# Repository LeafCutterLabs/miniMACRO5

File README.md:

# miniMACRO5
QMK-powered macropad based on Arduino Pro Micro. Supports a mix of up to 5 rotary encoders or mechanical switches with optional RGB underglow.

<br>

## Bill of materials (BOM)
### Required components
1. Arduino Pro Micro with headers - available from SparkFun, eBay, Amazon, etc.
2. Rotary encoders - Bourns PEC12R and PEC11R, Alps, and the cheap Chinese versions have been tested. Any quadrature encocder that fits should work. Supports switch encoders.
3. Cherry MX-style switches
4. Keycaps for your chosen switches
5. Case (3d printable STL in `/hardware`)
6. 4x 4mm M2 mounting screws
7. Electrical insulation tape (if you do not have any, at this low voltage and current, regular clear tape will suffice)

### Optional components
1. Reset switch (most 4pin 5.1 smd switches should work)
2. ICSP headers (only required to flash the Arduino if the Caterina bootloader is not present)
3. WS2812 LED strip (for RGB underglow)

## Assembly instructions
[See ASSEMBLY.md](ASSEMBLY.md) for build instructions with photos.

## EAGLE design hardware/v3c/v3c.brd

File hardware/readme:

The v3/v2 stl and laser files will work with v3b boards. The new v3b case includes a top plate.

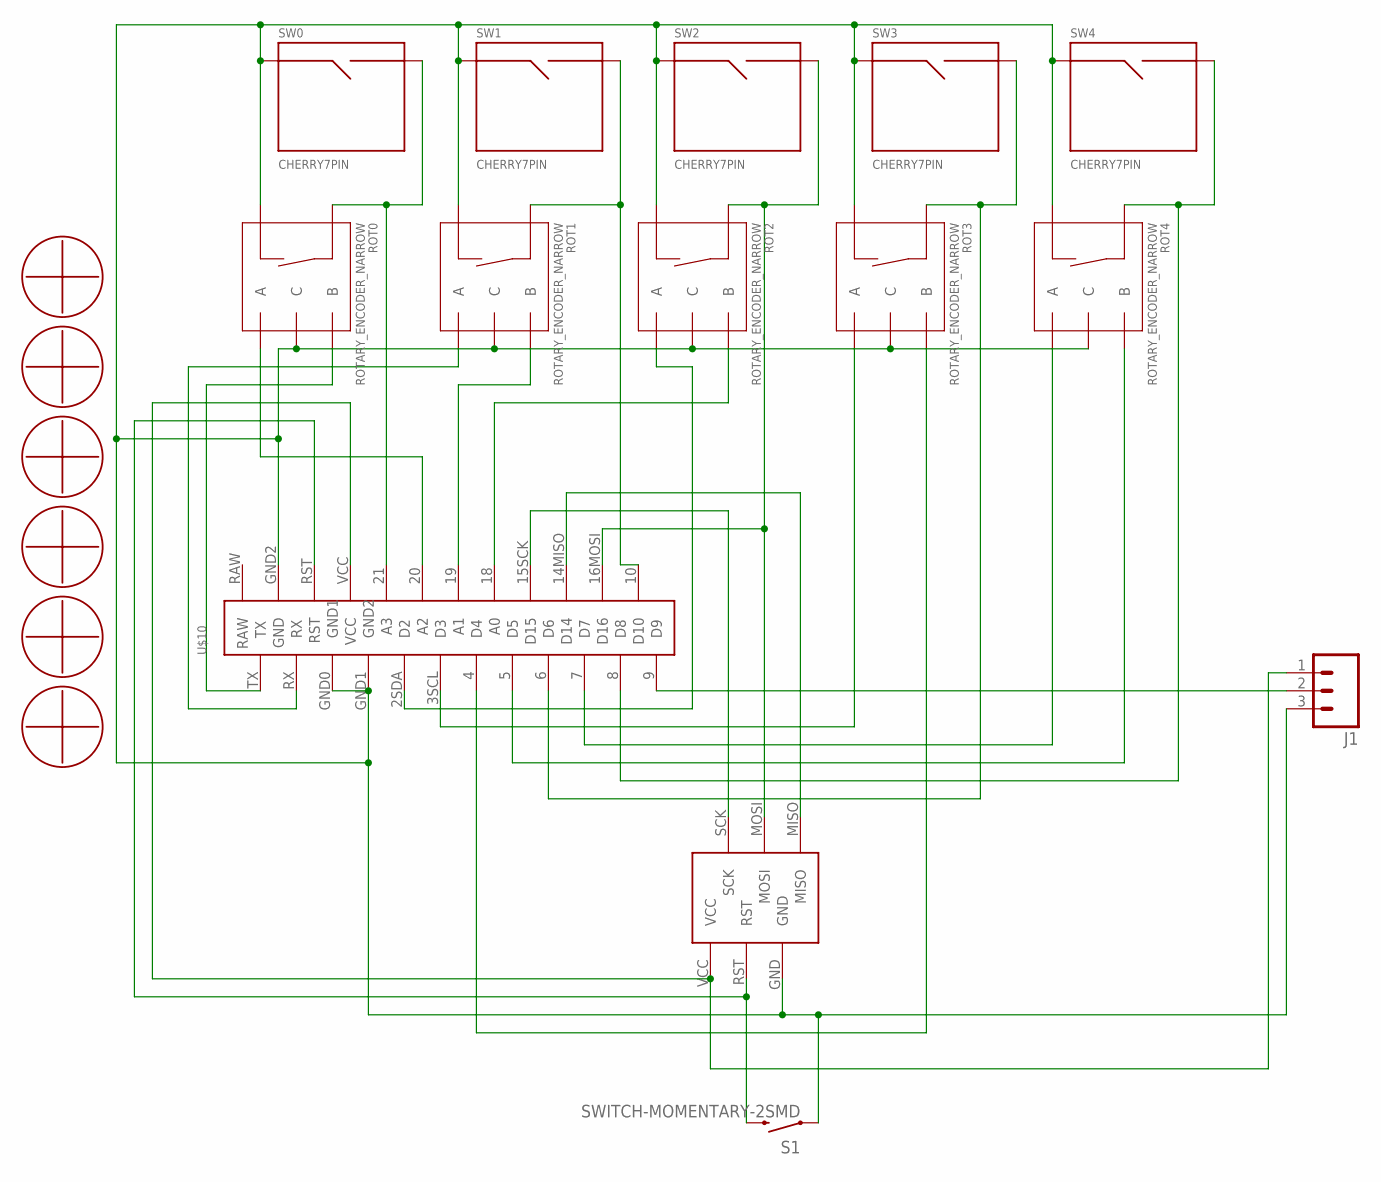
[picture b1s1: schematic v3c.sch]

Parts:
J1: M031X03_NO_SILK; 1X03_NO_SILK
ROT0, ROT1, ROT2, ROT3, ROT4: ROTARY_ENCODER_NARROW; ROTARY_ENC_NARROW
S1: SWITCH-MOMENTARY-2SMD; TACTILE_SWITCH_SMD
SW0, SW1, SW2, SW3, SW4: CHERRY7PIN; CHERRY5HOLE
U$1: ICSP
U$2, U$3, U$12, U$13, U$15, U$17: M2MOUNT
U$10: PROMICROLOCK; PROMICRO-LOCK

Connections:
2: ROT2.A, U$10.2SDA (D2)
3: ROT3.A, U$10.3SCL (D3)
4: ROT3.B, U$10.4 (D4)
5: ROT4.B, U$10.5 (D5)
6: ROT3.SW+, SW3.P$2 (SIG2), U$10.6 (D6)
7: ROT4.A, U$10.7 (D7)
8: ROT4.SW+, SW4.P$2 (SIG2), U$10.8 (D8)
10: ROT1.SW+, SW1.P$2 (SIG2), U$10.10 (D10)
18: ROT2.B, U$10.18 (A0)
19: ROT1.B, U$10.19 (A1)
20: ROT0.A, U$10.20 (A2)
21: ROT0.SW+, SW0.P$2 (SIG2), U$10.21 (A3)
GND: J1.3, ROT0.C, ROT0.SW-, ROT1.C, ROT1.SW-, ROT2.C, ROT2.SW-, ROT3.C, ROT3.SW-, ROT4.C, ROT4.SW-, S1.1, SW0.P$1 (SIG1), SW1.P$1 (SIG1), SW2.P$1 (SIG1), SW3.P$1 (SIG1), SW4.P$1 (SIG1), U$1.GND, U$10.GND0 (GND1), U$10.GND1 (GND2), U$10.GND2 (GND)
LEDOUT: J1.2, U$10.9 (D9)
MISO: U$1.MISO, U$10.14MISO (D14)
MOSI: ROT2.SW+, SW2.P$2 (SIG2), U$1.MOSI, U$10.16MOSI (D16)
RST: S1.3 (2), U$1.RST, U$10.RST
RX: ROT1.A, U$10.RX
SCK: U$1.SCK, U$10.15SCK (D15)
TX: ROT0.B, U$10.TX
VCC: J1.1, U$1.VCC, U$10.VCC

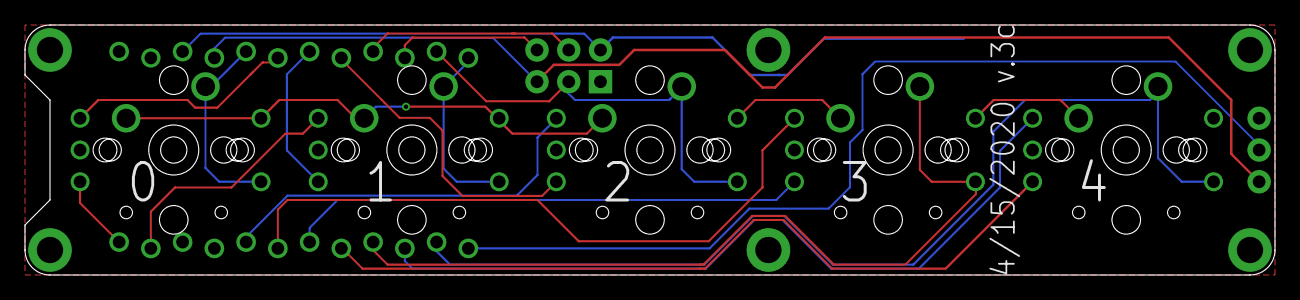
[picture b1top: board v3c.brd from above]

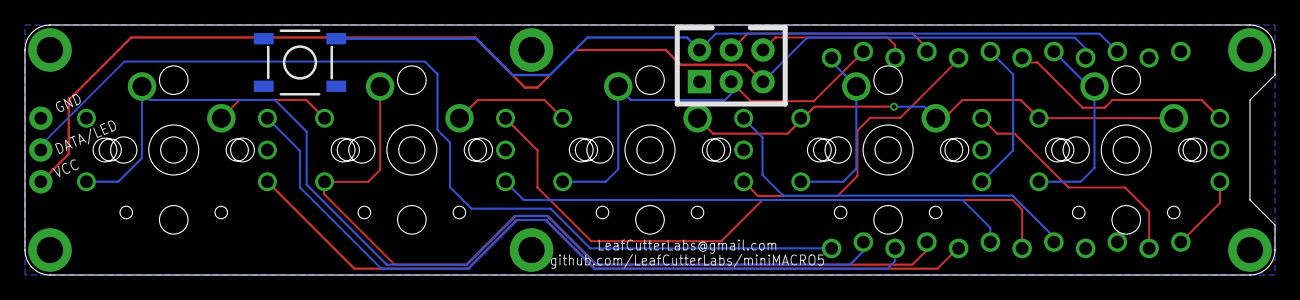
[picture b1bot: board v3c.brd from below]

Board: 2 copper layers, 100.0 x 20.0 mm, 20 parts (2 on the bottom side), 21 nets.

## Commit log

2020-02-17 Create placeholder
2020-02-20 Create place
2020-02-20 Create test
2020-02-20 Rename firmware/QMK/keymaps/default/keymap.c to firmware/QMKv2/keymaps/default/keymap.c
2020-02-20 Rename firmware/QMK/config.h to firmware/QMKv2/config.h
2020-02-20 Rename firmware/QMK/info.json to firmware/QMKv2/info.json
2020-02-20 Rename firmware/QMK/minimacro5.c to firmware/QMKv2/minimacro5.c
2020-02-20 Rename firmware/QMK/minimacro5.h to firmware/QMKv2/minimacro5.h
2020-02-20 Rename firmware/QMK/readme.md to firmware/QMKv2/readme.md
2020-02-20 Rename firmware/QMK/rules.mk to firmware/QMKv2/rules.mk
2020-03-04 Create QMKv3
2020-03-04 Create palceholder
2020-04-12 Fix description Arduino part name
2020-04-12 Updated BOM for clarity
2020-04-12 Correct typos
2020-04-16 Media Keymap and RGB underglow
    added media keymap and enabled tap dancing on key 4 (farthest from USB) - 2 quick presses turns off/on underglow, 3 quick presses changes RGB mode
2020-04-20 pre-compiled hex files
    Double press key farthest from usb to turn on RGB Tripple press to change mode
2020-04-24 added miniMACRO6
    firmware for miniMACRO6
2020-04-27 Fixed typos, caps and use Markdown to format
2020-05-12 Add files via upload
    fixed A and B encoder pads so Clockwise and Counter Clockwise worked correctly in the keymaps
2020-05-14 media keymap
    updates media keymap
    moved procompiled hex to new folder
2020-05-23 New V3 sketch
    Not tested and does not support LED underglow (arduino pin 9)
2020-05-27 updated config
2020-06-02 Fix typo, move and link assembly instructions
2020-06-02 Begin adding assembly instructions
2020-06-02 Re-order assembly instructions, add tips
2020-06-02 Add tape to the bill of materials
2020-06-04 v3b gerber
2020-06-04 Add clarity about tape usage
2020-06-07 Add instructions (WIP)
2020-06-07 Add photo (switches in plate)
2020-06-07 Add photo to instructions
2020-06-07 Minor changes to wording
2020-06-07 Convert photo readme to Markdown and update text
2020-06-07 Add v3bAssembly photo readme
2020-06-07 Update heading
2020-06-07 Add reset and ICSP instructions plus photos
2020-06-07 Add mounting description and photos
2020-06-07 Add USB insulation photo
2020-06-07 Add Pro Micro header photo
2020-06-07 Add encoder photo and instruction
2020-06-07 Add switch pin out and instructions
2020-06-07 Minor wording change
2020-06-07 Correct order for adding light strip
2020-06-07 Add Pro Micro soldering instructions
2020-06-07 Add mount instructions
2020-06-07 Mention pink supports
2020-06-07 Improve readability
2020-06-07 Fix typos and formatting
2020-06-07 Add equipment list
2020-06-07 Fix typo
2020-06-07 Add title
2020-06-08 Add tin snips
2021-01-09 added v3c gerber/eagle files
2022-07-07 Added reset switch detail to BOM
2023-03-27 Added note about GND pins shorting

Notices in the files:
parts and their libraries:
SparkFun-Connectors: Licensing: Creative Commons ShareAlike 4.0 International - https://creativecommons.org/licenses/by-sa/4.0
